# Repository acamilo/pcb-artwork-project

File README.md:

# pcb-artwork-project
These logos belong to thier owners and are not affilited with me in any way, I just thought they'd look cool on a PCB.

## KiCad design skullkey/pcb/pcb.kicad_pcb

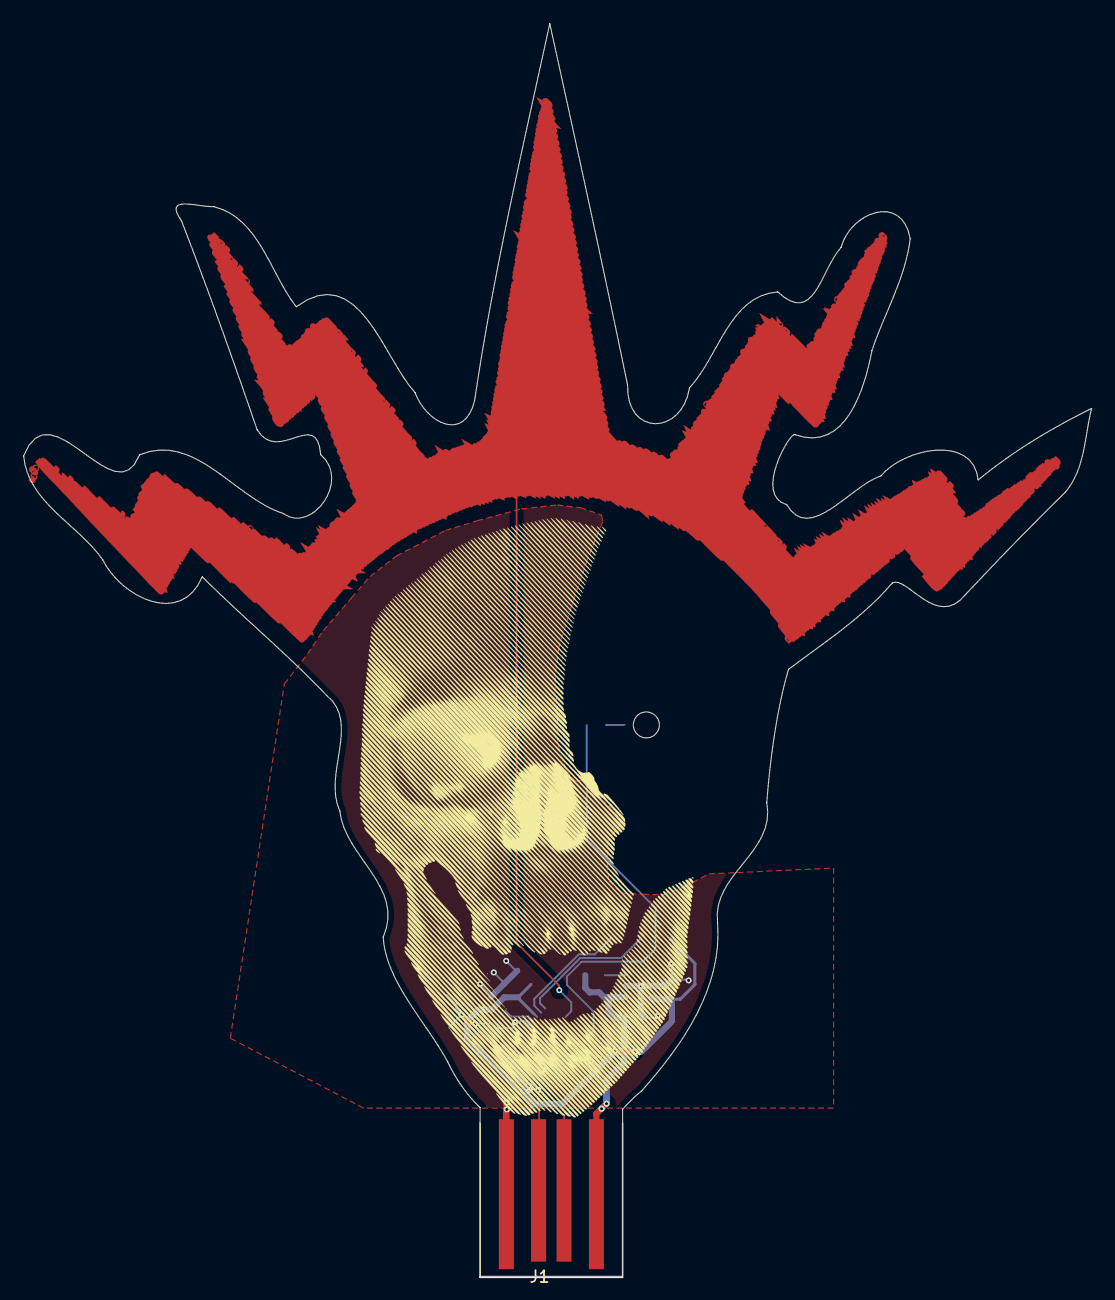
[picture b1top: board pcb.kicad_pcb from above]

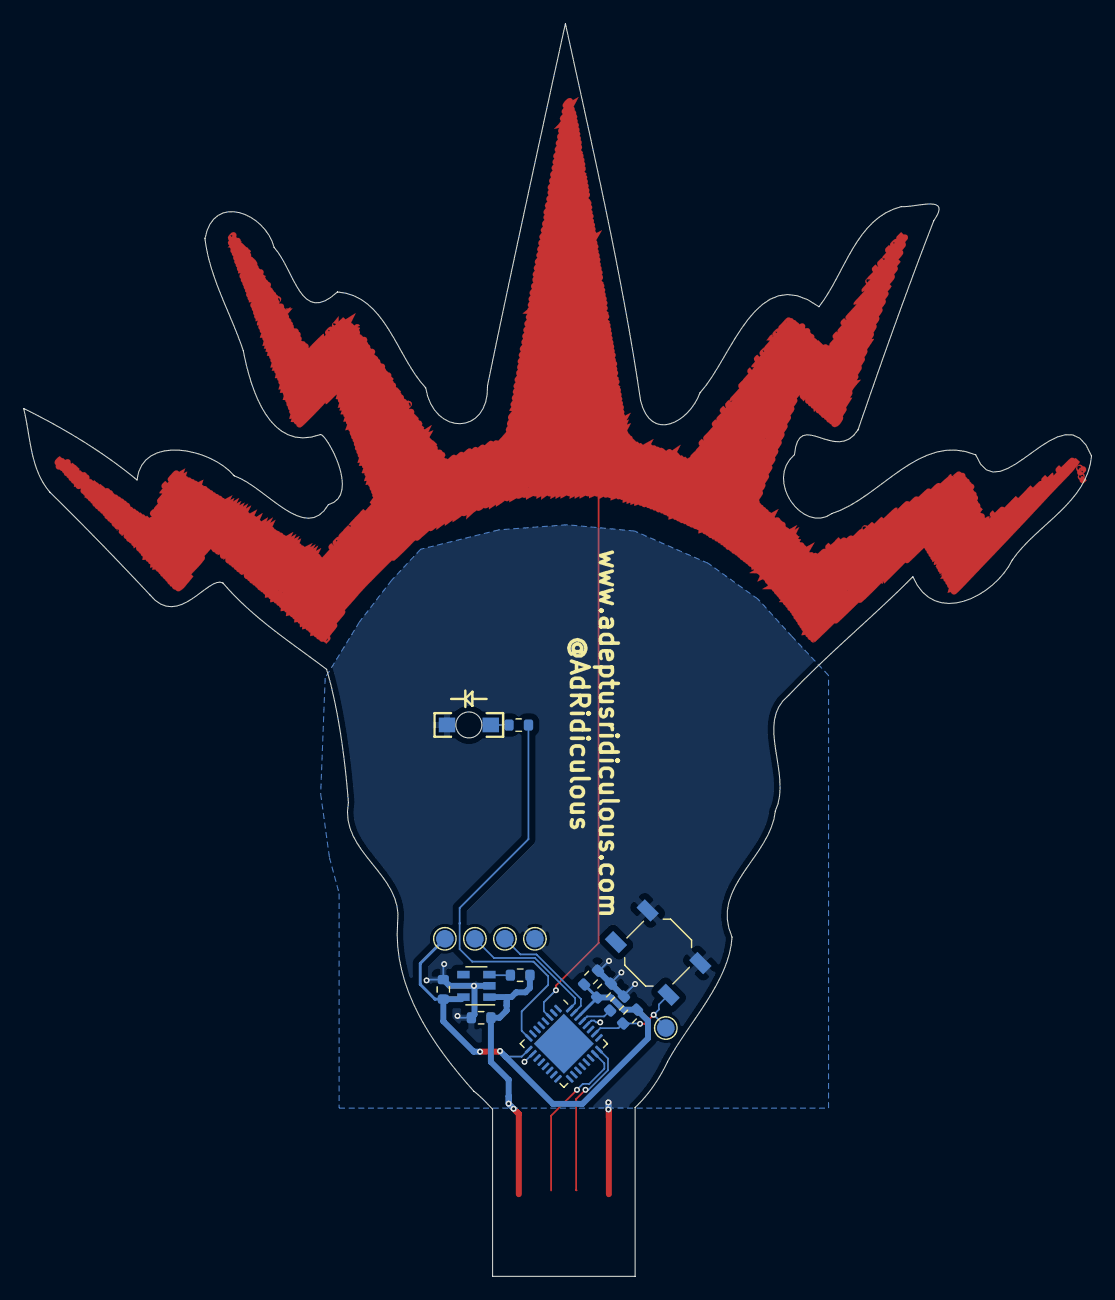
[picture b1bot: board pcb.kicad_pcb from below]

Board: 2 copper layers, 90.4 x 106.0 mm, 20 parts (17 on the bottom side), 12 nets.

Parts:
C1, C2, C6, C7: 10uF; R_0603_1608Metric
C3: 1uF; R_0603_1608Metric
J1: USB_B; usb-pcb
R1, R5: 100k; R_0603_1608Metric
R4: 330; R_0603_1608Metric
Ref**: Val**; skull-kicad
Ref**#2: Val**; skull-kicad
SW1: SW_SPST; SW_SPST_TL3342
TP1, TP2, TP3, TP4, TP5: TestPoint; TestPoint_Pad_D1.5mm
U1: ATSAMD21E18A-M; QFN-32-1EP_5x5mm_P0.5mm_EP3.6x3.6mm
U2: AP2112K-3.3; SOT-23-5
U5: HSMC-C265

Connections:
+3V3: C2.1, C3.1, C7.1, R5.2, TP1.1, U1.9, U1.30, U2.5
+5VP: C6.1, J1.1, R1.2, U2.1
D+: J1.3, U1.24
D-: J1.2, U1.23
GND: C1.1, C2.2, C3.2, C6.2, C7.2, J1.4, SW1.2, TP4.1, U1.10, U1.28, U2.2, U5.C
unnamed: C1.2, U1.29
unnamed: R1.1, U2.3
unnamed: R4.1, U5.A
unnamed: R4.2, U1.8
unnamed: R5.1, SW1.1, TP5.1, U1.26
unnamed: TP2.1, U1.31
unnamed: TP3.1, U1.32

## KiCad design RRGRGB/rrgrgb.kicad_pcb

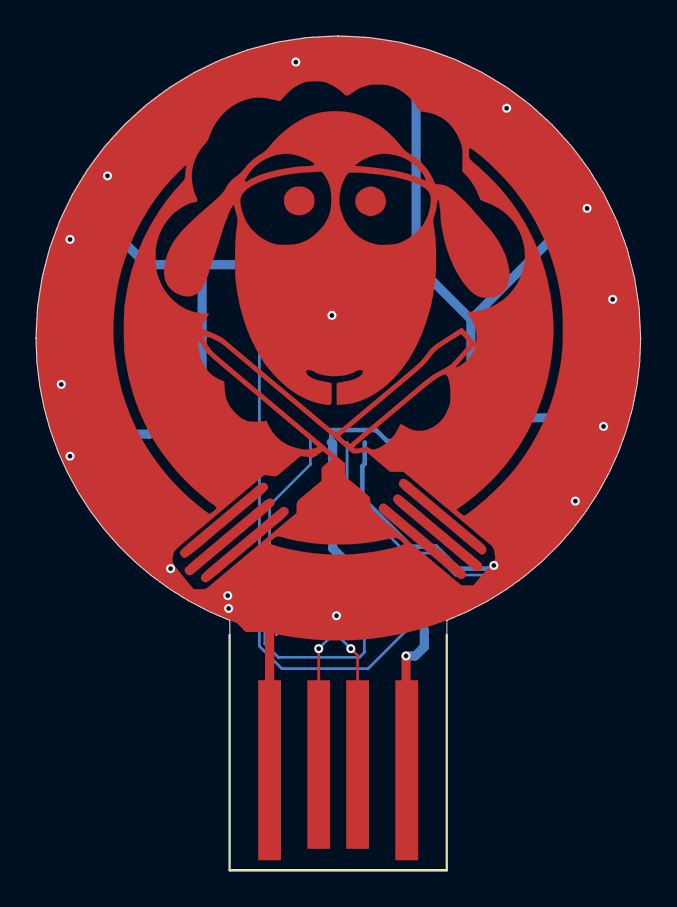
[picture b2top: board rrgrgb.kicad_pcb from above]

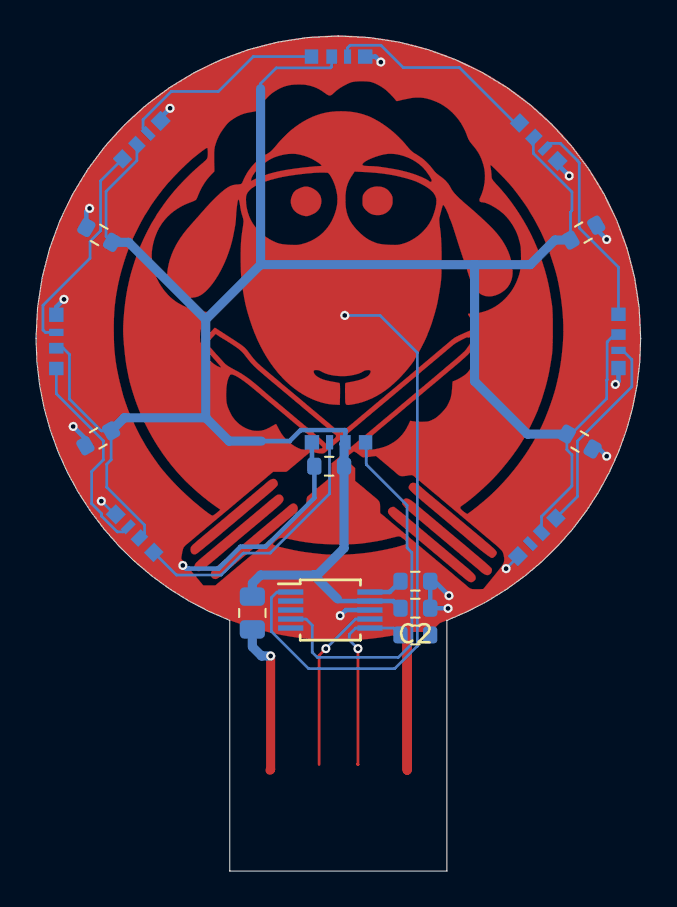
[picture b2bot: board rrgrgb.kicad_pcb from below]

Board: 2 copper layers, 33.6 x 46.4 mm, 20 parts (18 on the bottom side), 14 nets.

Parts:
C1, C2, C3, C4, C6, C7: 0.1uF; R_0603_1608Metric
CE: 0.1uF; R_0603_1608Metric
J1: USB_B; usb-pcb-short
R1: fuse; R_0805_2012Metric
R2: 10k; R_0603_1608Metric
Ref**: Val**; pcb-layers
U1, U3, U4, U5, U6, U7, U8, U9: SK68XX_SIDE
U2: CH552E; MSOP-10_3x3mm_P0.5mm

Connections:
+3V3: C1.2, U2.10
+5V: C2.2, C3.1, C4.1, C6.1, C7.1, CE.1, R1.1, U1.2, U2.9, U3.2, U4.2, U5.2, U6.2, U7.2, U8.2, U9.2
D+: J1.3, R2.2, U2.6
D-: J1.2, U2.7
GND: C1.1, C2.1, C3.2, C4.2, C6.2, C7.2, CE.2, J1.4, U1.4, U2.8, U3.4, U4.4, U5.4, U6.4, U7.4, U8.4, U9.4
unnamed: J1.1, R1.2
unnamed: U1.1, U9.3
unnamed: U3.3, U8.1
unnamed: U4.1, U7.3
unnamed: U4.3, U9.1
unnamed: U5.1, U8.3
unnamed: U5.3, U6.1
unnamed: U6.3, U7.1
neo: U2.4, U3.1
